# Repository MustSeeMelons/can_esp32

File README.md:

# CAN ESP32

The loose wire goes to 3rd pin from the bottom (DTR?).

## Summary

New cars do chimes when turning on the engine. My '06 Focus does not. This device aims to rectify that!
An ESP32 with an micro sd card reader, paired with a MAX9860 to play .wav files upon receiving certain CAN messages.
CAN connection handled by the TJA1050. Powered from the OBD2 port 12V rail, with two buck converters for 5V and 3V.

Is an AP that serves a Preact App for listening in on the CAN network via a websocket connection.

Avaialble through `obd2.local` with the help of mdns!

On plugging in plays the windows XP startup sound.

I don't get any OBD responses from my 2006 Focus, but I can clear DTC's!

Would need to decode raw CAN frames to make sense of anything.

## TODO
- [FW/FE] Read DTC
- [FW] Play audio on startup (800RPM) and shutdown (?) (0RPM).
- [FW] SD Card logger.
- [FE][FW] Oil Temp request/response, visualization.
- [XX] Update PCB [IC<>IC level shifter, CAN caps, 32[TX], 33[RX]]
- [FE] GZIP the Preact app
- [FW] Spiffs for web app storage?

- Plug in device to gather more data points - need to decipher the messages.

## Notes to future self

- Implement the upload mechanism that all ESP32 baords use. Turning things on/off is annoying.
- Serial monitoring during operation would be great!

## How to flash

1. Connect the FTDI FT232RL and power it on.
2. Connect 12V, GND leads and power on the power supply.
3. Turn off both, turn back the power supply.

### Dev Board

Keep down the boot button while powering on.

## Julie OBD2 emulator

RED: VCC
BLUE: GND
GREEN: CODE (UNCONNECTED/GND)
BLACK: CAN-H
WHITE: CAN-L

Sketchy link: https://lisaiauto.ru/universalnyj-emulyator-julie-of80-manual-po-nastrojke-i-podklyucheniyu/

## SPIFFS

## OBDII Response addresses 

`0x7DF` is a broadcast to all devices.
`0x7E8` should be the engine
`0x7e9` should be transmission

## Websocket

- Must enable WS in SDK
- Must increase HTTP URI Length in SDK

## TJA1050

TX & RX should be swapped when connecting - RX goes to TX, RX to TX as usual.

## SD Card

Files present on the SD card at `/`

- xp/oxp.wav
- xp/vistashutdown.wav

## VSC

Instal LLVM and use theclang-format extension for formatting. [link](https://github.com/llvm/llvm-project/releases/tag/llvmorg-20.1.0)

## IDF

ESP-IDF projects are built using CMake. The project build configuration is contained in `CMakeLists.txt`
files that provide set of directives and instructions describing the project's source files and targets
(executable, library, or both).

Below is short explanation of remaining files in the project folder.

```
├── CMakeLists.txt
├── main
│   ├── CMakeLists.txt
│   └── main.c
└── README.md                  This is the file you are currently reading
```

Additionally, the sample project contains Makefile and component.mk files, used for the legacy Make based build system.
They are not used or needed when building with CMake and idf.py.

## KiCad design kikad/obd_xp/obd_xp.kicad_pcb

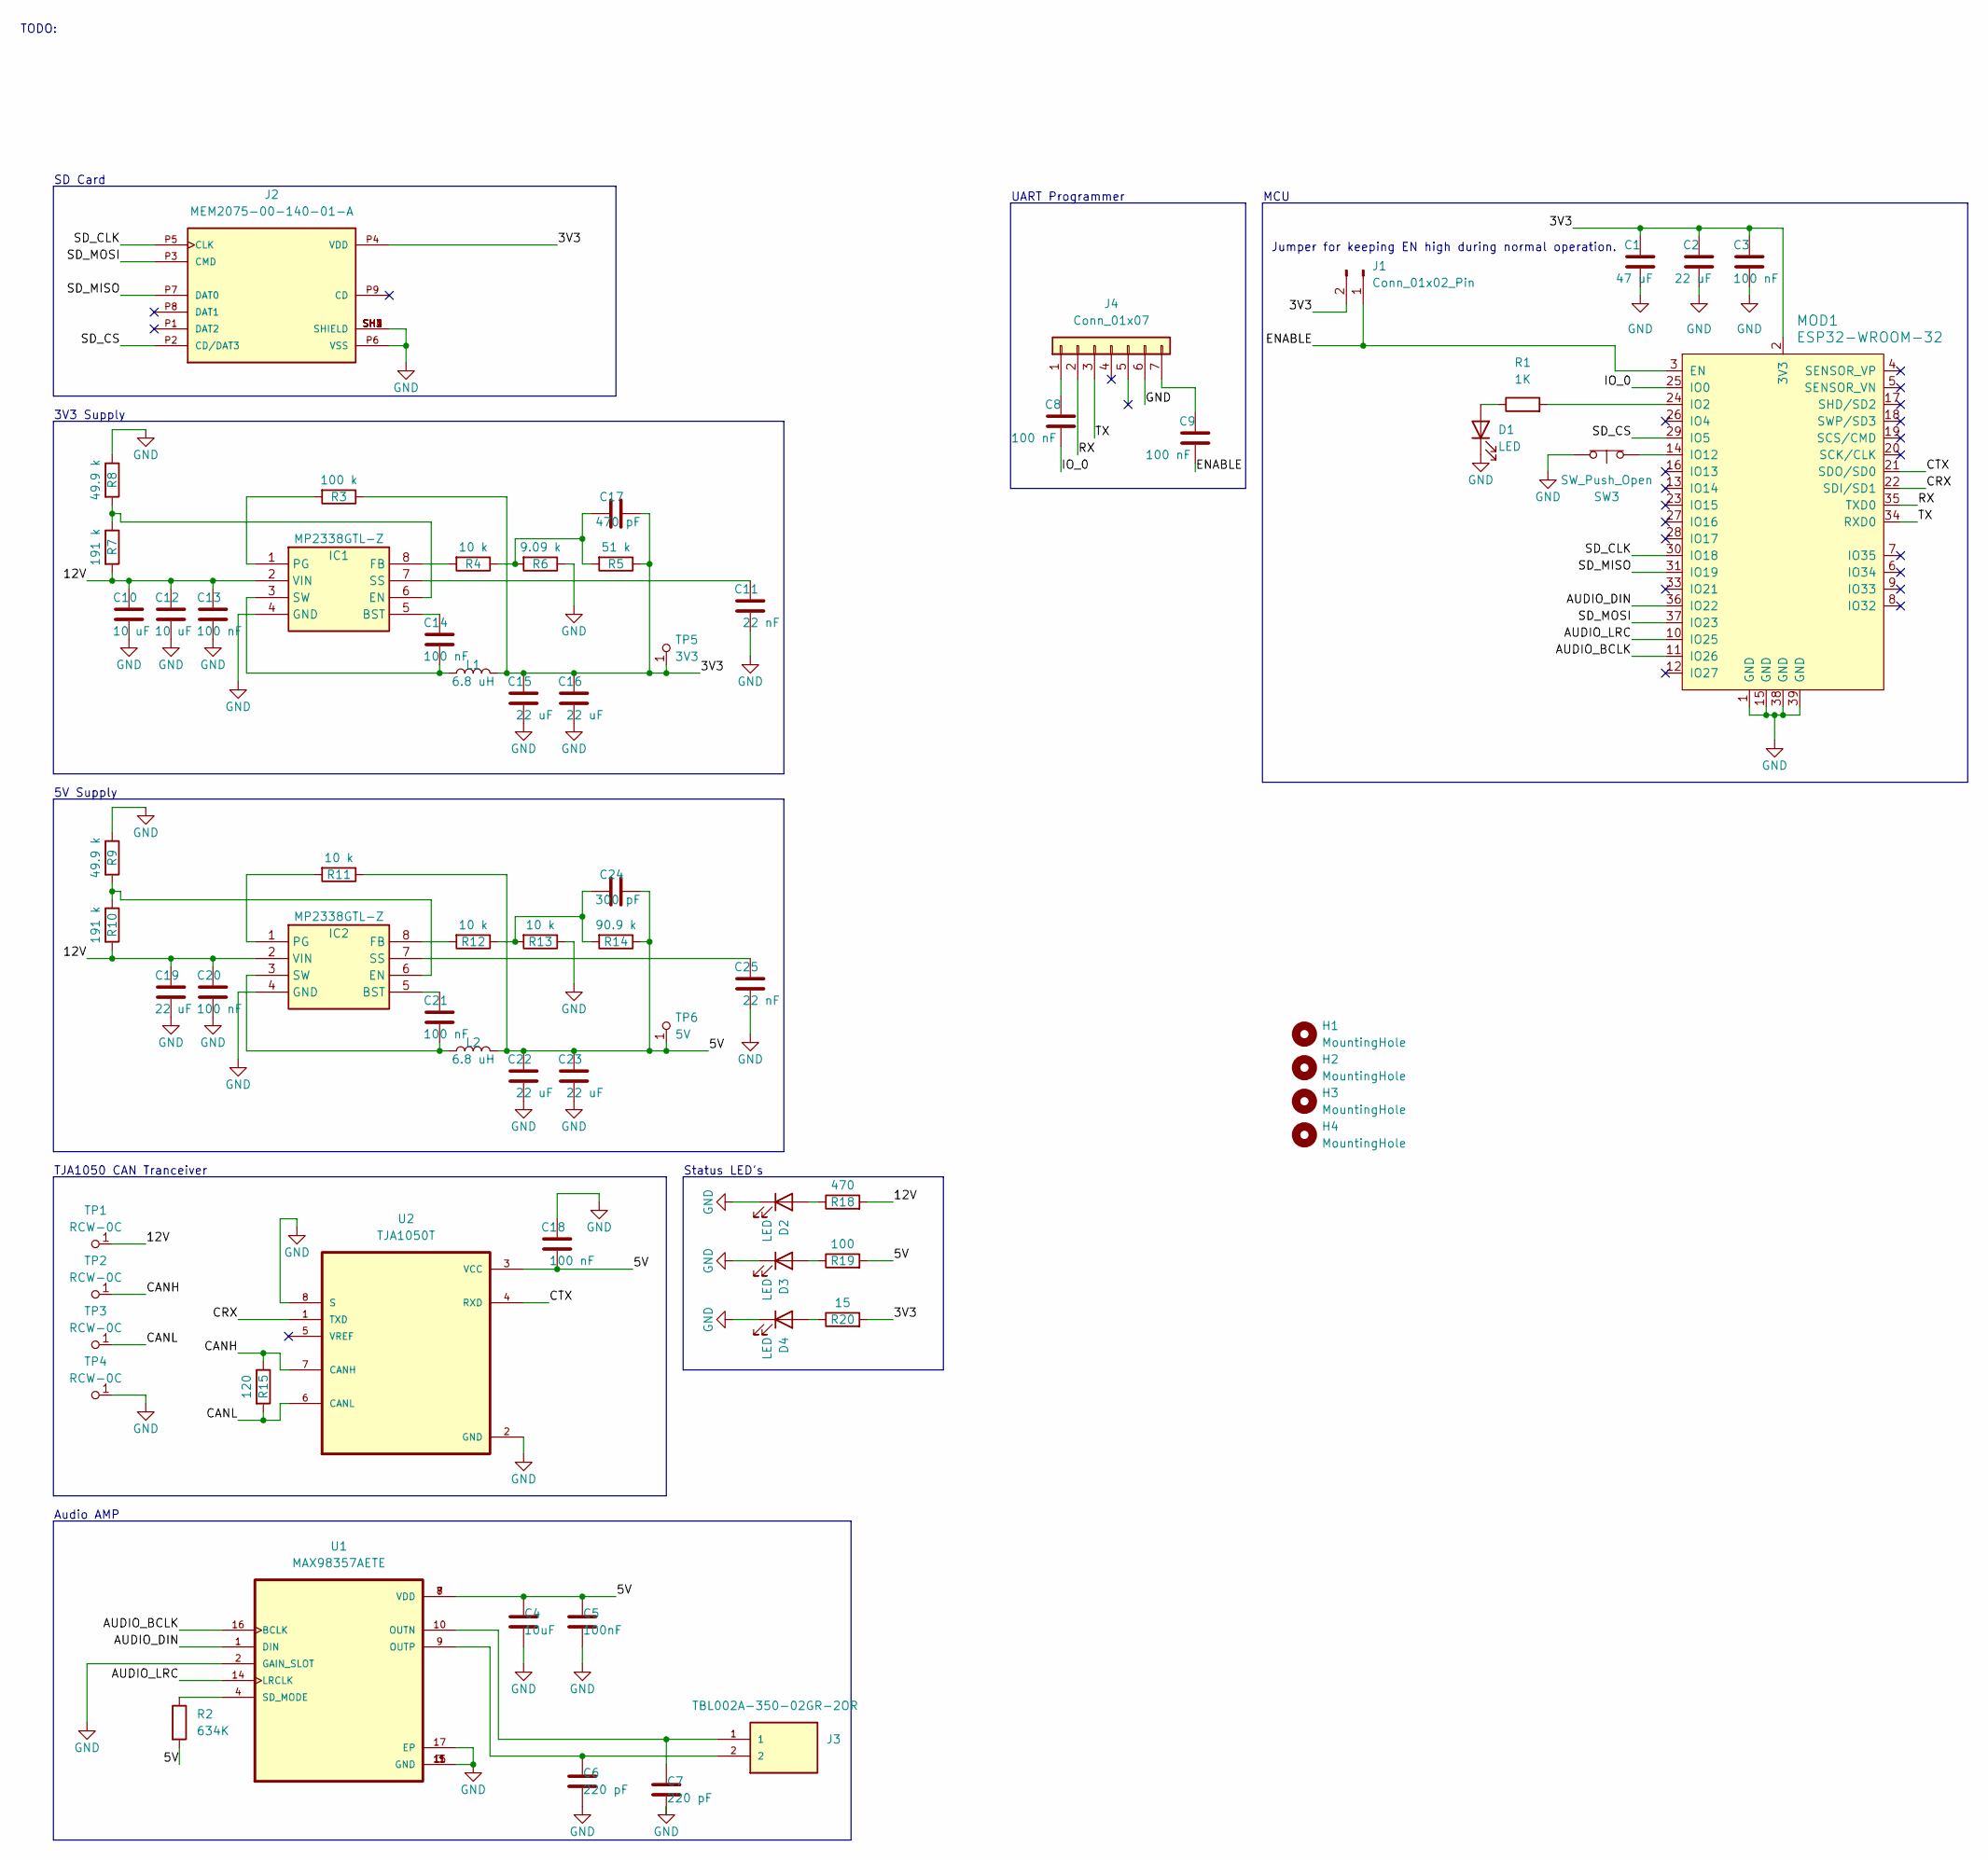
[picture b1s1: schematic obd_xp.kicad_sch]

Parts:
C1: 47 uF; C_0805_2012Metric
C2, C15, C16, C19, C22, C23: 22 uF; C_0805_2012Metric
C3, C8, C9, C13, C14, C18, C20, C21: 100 nF; C_0805_2012Metric
C4: 10uF; C_0805_2012Metric
C5: 100nF; C_0805_2012Metric
C6, C7: 220 pF; C_0805_2012Metric
C10, C12: 10 uF; C_0805_2012Metric
C11, C25: 22 nF; C_0805_2012Metric
C17: 470 pF; C_0805_2012Metric
C24: 300 pF; C_0805_2012Metric
D1, D2, D3, D4: LED; LED_0805_2012Metric
H1, H2, H3, H4: MountingHole; MountingHole_3.2mm_M3
IC1, IC2: MP2338GTL-Z; MP2338GTLZ; Mouser Part Number 946-MP2338GTL-Z
J1: Conn_01x02_Pin; PinHeader_1x02_P2.54mm_Vertical
J2: MEM2075-00-140-01-A; GCT_MEM2075-00-140-01-A; PARTREV A
J3: TBL002A-350-02GR-2OR; CUI_TBL002A-350-02GR-2OR; PARTREV 1.0
J4: Conn_01x07; PinHeader_1x07_P2.54mm_Vertical
L1, L2: 6.8 uH; L_SOREDE_SNR.1050_10x10x5mm
MOD1: ESP32-WROOM-32; ESP32-WROOM-32D; MPN ESP32-WROOM-32; Digi-Key_PN 1904-1010-1-ND
R1: 1K; R_0805_2012Metric
R2: 634K; R_0805_2012Metric
R3: 100 k; R_0805_2012Metric
R4, R11, R12, R13: 10 k; R_0805_2012Metric
R5: 51 k; R_0805_2012Metric
R6: 9.09 k; R_0805_2012Metric
R7, R10: 191 k; R_0805_2012Metric
R8, R9: 49.9 k; R_0805_2012Metric
R14: 90.9 k; R_0805_2012Metric
R15: 120; R_0805_2012Metric
R18: 470; R_0805_2012Metric
R19: 100; R_0805_2012Metric
R20: 15; R_0805_2012Metric
SW3: SW_Push_Open; SW_PUSH_6mm
TP1, TP2, TP3, TP4: RCW-0C; PROBE_PAD_1206; MPN RCW-0C; Digi-Key_PN A106146CT-ND
TP5: 3V3; PROBE_PAD_1206; MPN RCW-0C; Digi-Key_PN A106146CT-ND
TP6: 5V; PROBE_PAD_1206; MPN RCW-0C; Digi-Key_PN A106146CT-ND
U1: MAX98357AETE; QFN50P300X300X80-17N
U2: TJA1050T; SOIC127P599X175-8N

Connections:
/3V3: C1.1, C2.1, C3.1, C15.1, C16.1, C17.2, J1.2, J2.P4 (VDD), L1.2, MOD1.2 (3V3), R3.1, R5.1, R20.2, TP5.1
/5V: C4.1, C5.1, C18.2, C22.1, C23.1, C24.2, L2.2, R2.2, R11.1, R14.1, R19.2, TP6.1, U1.7 (VDD), U1.8 (VDD), U2.3 (VCC)
/12V: C10.1, C12.1, C13.1, C19.1, C20.1, IC1.2 (VIN), IC2.2 (VIN), R7.2, R10.2, R18.2, TP1.1
/AUDIO_BCLK: MOD1.11 (IO26), U1.16 (BCLK)
/AUDIO_DIN: MOD1.36 (IO22), U1.1 (DIN)
/AUDIO_LRC: MOD1.10 (IO25), U1.14 (LRCLK)
/CANH: R15.1, TP2.1, U2.7 (CANH)
/CANL: R15.2, TP3.1, U2.6 (CANL)
/CRX: MOD1.22 (SDI/SD1), U2.1 (TXD)
/CTX: MOD1.21 (SDO/SD0), U2.4 (RXD)
/ENABLE: C9.2, J1.1, MOD1.3 (EN)
/IO_0: C8.2, MOD1.25 (IO0)
/RX: J4.2, MOD1.35 (TXD0)
/SD_CLK: J2.P5 (CLK), MOD1.30 (IO18)
/SD_CS: J2.P2 (CD/DAT3), MOD1.29 (IO5)
/SD_MISO: J2.P7 (DAT0), MOD1.31 (IO19)
/SD_MOSI: J2.P3 (CMD), MOD1.37 (IO23)
/TX: J4.3, MOD1.34 (RXD0)
GND: C1.2, C2.2, C3.2, C4.2, C5.2, C6.2, C7.2, C10.2, C11.2, C12.2, C13.2, C15.2, C16.2, C18.1, C19.2, C20.2, C22.2, C23.2, C25.2, D1.1 (K), D2.1 (K), D3.1 (K), D4.1 (K), IC1.4 (GND), IC2.4 (GND), J2.P6 (VSS), J2.SH1 (SHIELD), J2.SH2 (SHIELD), J2.SH3 (SHIELD), J2.SH4 (SHIELD), J4.6, MOD1.1 (GND), MOD1.15 (GND), MOD1.38 (GND), MOD1.39 (GND), R6.1, R8.1, R9.1, R13.1, SW3.1 (A), TP4.1, U1.2 (GAIN_SLOT), U1.3 (GND), U1.11 (GND), U1.15 (GND), U1.17 (EP), U2.2 (GND), U2.8 (S)
unnamed: C17.1, R4.1, R5.2, R6.2
unnamed: C24.1, R12.1, R13.2, R14.2
unnamed: D1.2 (A), R1.1
unnamed: D2.2 (A), R18.1
unnamed: D3.2 (A), R19.1
unnamed: D4.2 (A), R20.1
unnamed: C14.1, IC1.5 (BST)
unnamed: IC1.6 (EN), R7.1, R8.2
unnamed: IC1.8 (FB), R4.2
unnamed: IC1.1 (PG), R3.2
unnamed: C11.1, IC1.7 (SS)
unnamed: C14.2, IC1.3 (SW), L1.1
unnamed: C21.1, IC2.5 (BST)
unnamed: IC2.6 (EN), R9.2, R10.1
unnamed: IC2.8 (FB), R12.2
unnamed: IC2.1 (PG), R11.2
unnamed: C25.1, IC2.7 (SS)
unnamed: C21.2, IC2.3 (SW), L2.1
unnamed: C8.1, J4.1
unnamed: C9.1, J4.7
unnamed: MOD1.24 (IO2), R1.2
unnamed: MOD1.14 (IO12), SW3.2 (B)
unnamed: C7.1, J3.1, U1.10 (OUTN)
unnamed: C6.1, J3.2, U1.9 (OUTP)
unnamed: R2.1, U1.4 (SD_MODE)

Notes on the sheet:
3V3 Supply
Status LED's
TODO:
TJA1050 CAN Tranceiver
Jumper for keeping EN high during normal operation.
5V Supply
SD Card
Audio AMP
UART Programmer
MCU

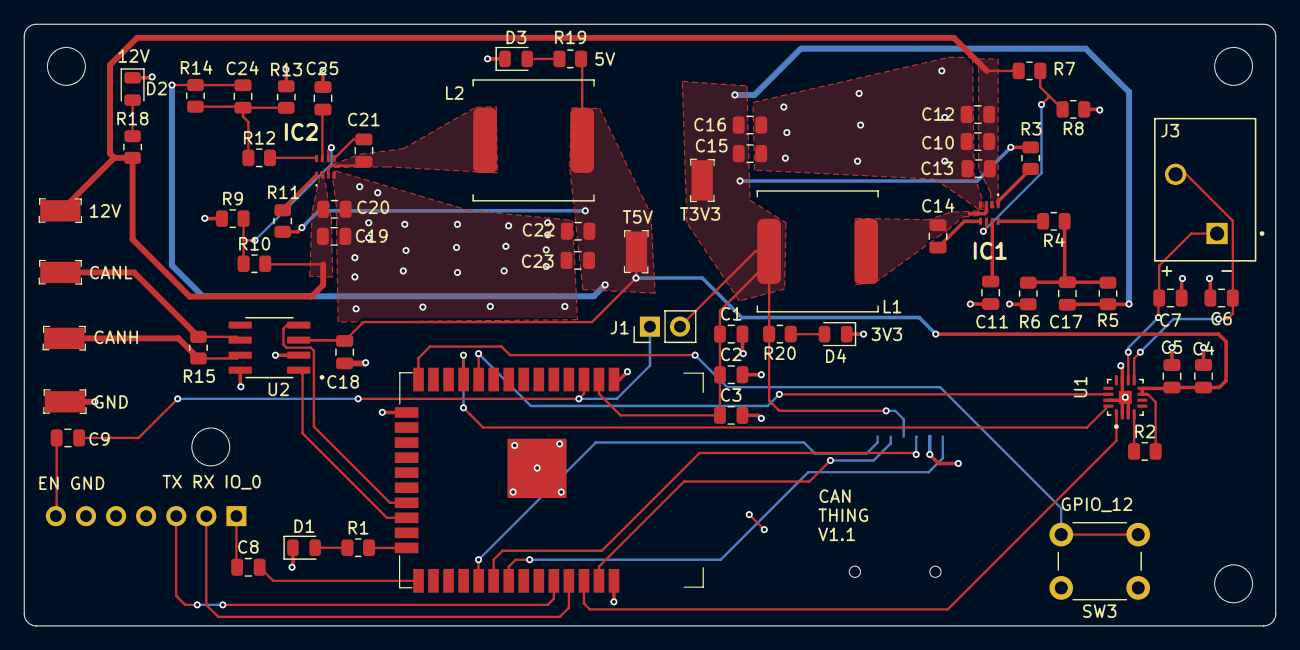
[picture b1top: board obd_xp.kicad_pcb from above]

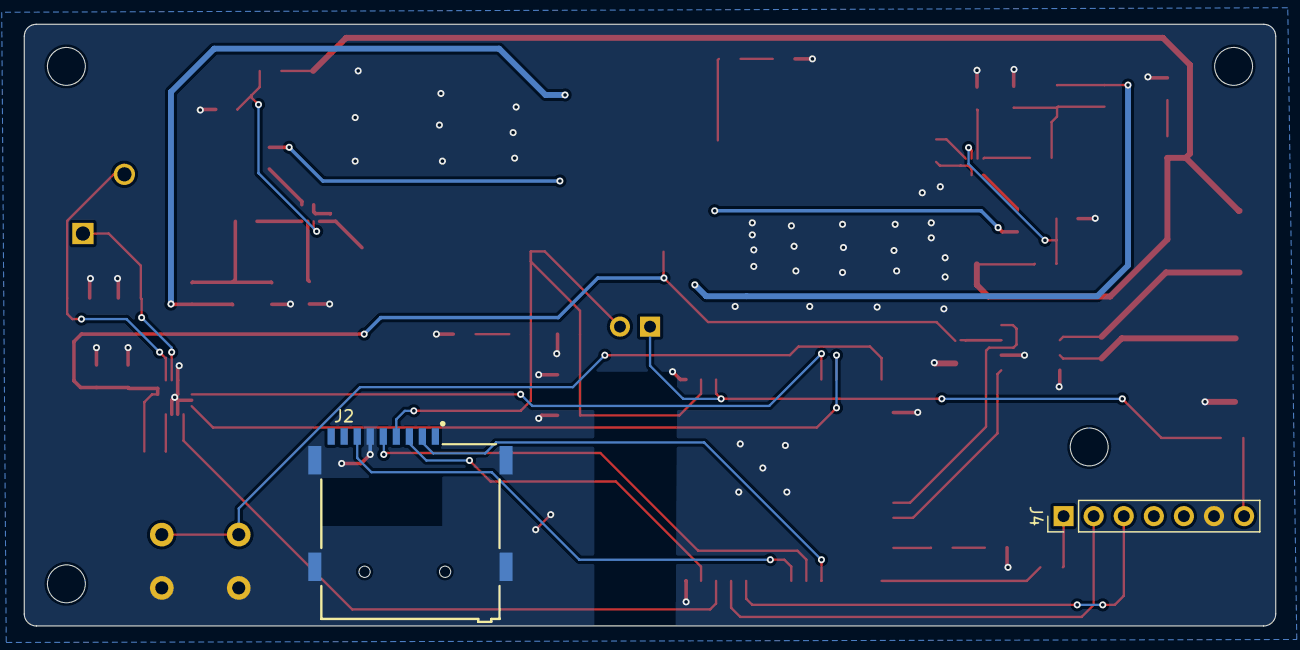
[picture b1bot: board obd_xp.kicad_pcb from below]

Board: 2 copper layers, 105.7 x 50.8 mm, 69 parts (2 on the bottom side), 44 nets.

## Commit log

2025-01-22 Initial
2025-02-20 Split into tasks
2025-03-16 AP,HTTP Server,mDNS
2025-03-16 Serve Preact app
2025-03-20 WS setup
2025-04-06 Render out CAN messages in a basic way
2025-04-06 Made CAN messages more readable
2025-04-07 Save as JSON + routes
2025-04-13 Update monitor view
2025-04-21 Finilazy CAN pins, WIP http server messaging, add pinout
2025-05-26 Simple WAV playback test
2025-05-28 WIP of multi task wav playback
2025-05-29 Split playback into two tasks
2025-06-04 2Q Playback
2025-06-19 Move things around
2025-07-07 Clear button + transparent button type
2025-07-07 Fix SD SPI bad retry
2025-07-10 Add storybook
2025-07-12 Portal & Anchor components
2025-07-22 Anchoer update, modal mechanism and outside click hook
2025-07-31 Action Menu Component
2025-08-01 Send CAN message (successfully)
2025-08-05 Action Modal WIP
2025-08-06 Clear DTC button flow
2025-08-07 DTC on demand
2025-08-10 Action Modal smol refactor
2025-08-12 Checkbox & message filter
2025-08-12 Use the new util
2025-08-14 RPM request
